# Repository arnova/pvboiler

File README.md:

# Open-source ESP PV-Boiler Controller

> ⚠️ **WARNING: HAZARDOUS VOLTAGES**
>
> This project is provided "as-is" and is to be used entirely at your own risk! The hardware is connected to the mains and involves voltages that may be lethal. Only build, install and service it if you are qualified to work on mains equipment, and always disconnect it from the mains before opening the enclosure.
>
> - The ESP/low-voltage side of the controller is galvanically isolated from the mains. Nevertheless, treat everything as live and dangerous!
> - Mount the controller in a closed plastic enclosure and earth the heatsink properly to the mains ground.
> - Only connect the controller to a correctly fused circuit.
> - The boiler's own thermostat and thermal cutoff must remain in the heating circuit. This controller is not a substitute for over-temperature protection!

This project is a complete hardware, firmware & software solution to turn your "dumb" electronic domestic hot water boiler into a smart **PV-Boiler**. It aims to optimize the amount of surplus solar electricity that can be stored in a boiler as hot water using as little grid power as possible.

Most other solutions use SSR modules for power control. This design uses a (BTA25/BTA40) **triac** for power control to enable **phase-angle control**, which allows for more accurate power control than with a normal SSR.

The hardware was designed using **KiCAD**, and the software uses **MQTT** for communication, targeted to be used with **Home Assistant**. The hardware and firmware were developed for either a NodeMCU v2 (Amica) ESP8266 module or an ESP32-DevKit (e.g. Olimex) module, but should in principle work with any ESP8266 or ESP32 board. Obviously, ESP boards with alternative form factors and/or pinouts cannot be directly fitted on the PCB but should be connected using wires, and you may need to modify platformio.ini and the GPIO definitions in include/system.h for your specific ESP board.

## Features

- Home Assistant (MQTT) support
- Phase angle control (default) or SSR dim style
- Configuration via USB serial connection or network terminal connection (port 8000)
- OTA updates (via PlatformIO)
- Support for an optional one-wire DS18B20 temperature sensor (probe) for sensing the boiler's internal temperature
- Automatic legionella prevention (using the optional one-wire temperature sensor). Danger zone temperatures, disinfection interval, duration and temperature are configurable via the terminal (see `exhelp`)
- Operating modes: automatic power budget mode (using e.g. P1/HA information), (manual) power percentage mode, boost mode (100% power, ignores software thermostat), standby mode (output off, legionella protection remains active) and off mode (output off, including legionella protection). The mode can be dynamically changed using MQTT
- Setpoint (software thermostat) modes (require the optional one-wire temperature sensor):
  - "Setpoint": always heats (100%) until the software thermostat setpoint is reached
  - "Budget up to Setpoint" / "Percentage up to Setpoint": like budget/percentage mode, but heating stops at the software thermostat setpoint
  - "Setpoint, then Budget": always heats (100%) until the software thermostat setpoint is reached; above it, surplus budget is used to heat further (up to the boiler's own thermostat)
  - "Percentage to Setpoint, then Budget": heats at the set percentage until the software thermostat setpoint is reached; above it, surplus budget is used to heat further (up to the boiler's own thermostat)
- Boiler overheating-protection (using the optional one-wire temperature sensor) in case the boiler hardware thermostat/protection somehow fails
- Support for directly communicating with DSMR-Reader (using MQTT) without e.g. Home Assistant
- Support for an optional OLED 128×64 screen to display output power/percentage, temperature and connection status
- The controller has a network watchdog. If there hasn't been any MQTT traffic to the controller for a while (e.g. when the network fails), the output will automatically decrease to 0% instead of being stuck on the last value. This behaviour can be disabled/configured with the `netwdt` and `netwdr` commands.

## Planned features & improvements

- Support for a CT current clamp
- Standalone support for more P1 providers

## Known issues

- During development it turned out that due to the ESP8266's single-core architecture WiFi interferes with accurate interrupt timing, causing problems with zero-cross detection and triac gate firing. Mitigations are in place but they can't completely fix the issue. Therefore for new designs it's recommended to use an ESP board with a dual-core ESP32-S3, ESP32-WROOM or ESP32-Wrover like the Olimex ESP32-DevKit-Lipo. Note that single-core ESP32 variants (e.g. ESP32-C3, ESP32-S2) share the ESP8266's limitation.

## Electromagnetic compatibility

Phase-angle control inherently generates harmonics and electromagnetic interference, because the triac switches the load on part-way through each mains half-cycle. The design includes an RC snubber across the triac and a 2-stage mains filter to limit this. Although such mains filters are expensive, do not omit them: consider the filter mandatory. Depending on your country and installation, regulations on conducted emissions and flicker (e.g. the EN 61000-3 series in the EU) may still apply to the complete installation, so check them before putting the device into permanent use.

## Hardware Assembly Hints

1. In the pictures-folder of this project you can find photos of my assembled enclosure which can be used as a guideline to build your own device
2. Use a sufficiently sized heatsink with a little thermal compound for mounting the BTA-triac. Generally it is recommended to use a heatsink with a thermal resistance better than 1.0 °C/W when using a ~2500 W boiler. Don't forget to connect the heatsink to the mains ground for safety! You should also use triacs with an electrically insulated tab, like the BTA-type triacs in the design
3. Around some power traces the mask has been intentionally left out. You should solder these traces with extra solder to reduce the power losses due to trace resistance
4. It is recommended to use 1.5 mm² flexible wires for internal wiring
5. When using the optional one-wire DS18B20 temperature sensor (probe) there are a few things you must adhere to make it work properly. Its supply should be connected to the board's +5V (not +3.3V), and the cable's ground shield should be connected to the (digital) low-voltage ground (NOT the mains ground) of the board. Most (sealed) temperature probes use a metal probe housing which is connected to the cable shield. Since this may short to the mains ground and introduce (switching) noise into the system, it should be isolated. The easiest way to accomplish this is using some shrink-tube
6. The electronics are designed for ~230/240 VAC grids. For other (lower) grid voltages some resistors (R1, R2, R11) need to be modified
7. The controller can only be connected directly to the normal mains connections of "dumb" hot water boilers. Boilers featuring any kind of (digital) electronics (except for an analog thermostat) require a modification of the boiler's internal wiring, see [Boilers with built-in electronics](#boilers-with-built-in-electronics)

## Boilers with built-in electronics

For boilers with (digital) electronics the controller cannot be connected to the boiler's normal mains connections. Instead, the controller must be placed in series with the boiler's heating element. This requires modifying the boiler's internal wiring:

1. Disconnect the boiler from the mains and make sure it cannot be switched on accidentally.
2. Of the 2 wires of the (internal) heating element(s), identify the one that is connected to the (safety) thermostat. This wire, and therefore the thermostat, must remain untouched.
3. Cut the other wire (the one NOT connected to the thermostat) in two. Connect only the end that goes to the heating element to the controller's TRIAC-L terminal.
4. Power the controller in one of these ways:
   - **Recommended: from the cut wire.** Connect the other cut end (the one coming from the boiler) to the controller's MAINS-L terminal, and connect the controller's MAINS-N terminal to the boiler's N (the connection the thermostat-side element wire returns to). The controller then only needs this one additional N connection. Because the controller takes its L from the same wire that used to feed the element, the L/N polarity pitfall of the separate feed option is avoided, which makes this option much more fool-proof. The cut end goes directly to the boiler's L input and is therefore permanently live; verify this with a multimeter before connecting.
   - **Separate feed.** Connect the controller's MAINS-L and MAINS-N terminals to the boiler's mains L and N, and properly insulate the unused cut end. Make sure the boiler's mains L/N connections are such that the controller's MAINS-L is the same "L" that used to feed the cut wire. Otherwise you create a short between the mains N and L.

Things to be aware of:

- The separate feed option is only suitable for a fixed (hard-wired) installation with verified polarity. Do **not** use it with a reversible plug (e.g. Schuko) where L and N are undefined. Always verify L and N with a multimeter.
- The boiler's own electronics may react unexpectedly to the modification (e.g. by reporting a fault when the element is not powered). This is boiler-dependent.
- Modifying a boiler's internal wiring may void its warranty and, depending on your country, may need to be performed by a qualified electrician.

Only do this when you have sufficient confidence you understand what you are doing!

## First Time Use

1. Flash the ESP firmware using PlatformIO. The initial flash needs to be performed using the USB serial connection, with one of the `usb-xxxxx` (`usb-esp8266` or `usb-esp32`) PlatformIO-environments: `pio run -e usb-xxxxx -t upload`. You may need to customize `platform` and `board` in your `platformio.ini` for your specific ESP board first.
2. After the initial flash, future firmware updates can be done over-the-air (OTA) with one of the `ota-xxxxx` (`ota-esp8266` or `ota-esp32`) PlatformIO-environments: `pio run -e ota-xxxxx -t upload`. Note that you *may* need to substitute the controller's IP address for `pvboiler.local` in `upload_port` of the relevant `ota-xxxxx` environment in case mDNS is not available in your network (or it's failing somehow).
3. Connect to the microcontroller's terminal interface, either via the USB connection or a socket connection to the device's IP at port 8000, using a terminal program (e.g. PuTTY). The network terminal is plain-text and also gives access to the stored WiFi and MQTT credentials, so only use it on a network you trust.
4. In the command terminal, `help` (+ `Enter`) will show all available commands with their descriptions. Initially, these operations must be performed:
   - Reset all settings to default with the `factoryreset`-command.
   - Set your WiFi network SSID with the `ssid`-command, providing the name of your network as an argument.
   - Set your WiFi network password with the `pass`-command, providing your network's security password as an argument. You may provide a zero-length value when your network requires no password.
   - Set your MQTT server IP with the `serverip`-command, providing the server IP as an argument.
   - Set your MQTT server username with the `mqttuser`-command. You may provide a zero-length value when your server requires no username.
   - Set your MQTT server password with the `mqttpass`-command. You may provide a zero-length value when your server requires no password.
   - Set boiler power rating with the `boiler`-command, providing the power rating of your boiler as an argument (the factory default is 2500 W).

> **Notes**
>
> - Only change other settings when you understand what they do!
> - When using budget logic mode, you must regularly (at least at 5-second intervals is recommended) tell the PvBoiler controller how much "budget" (= excess solar PV electricity) is available, e.g. from Home Assistant. A sample automation for Home Assistant can be found in the `home assistant` folder. Alternatively, use the terminal command `budgetsrc dsmr` to let the controller calculate the budget itself from DSMR-reader's MQTT topics (`dsmr/reading/electricity_currently_delivered` and `dsmr/reading/electricity_currently_returned`).

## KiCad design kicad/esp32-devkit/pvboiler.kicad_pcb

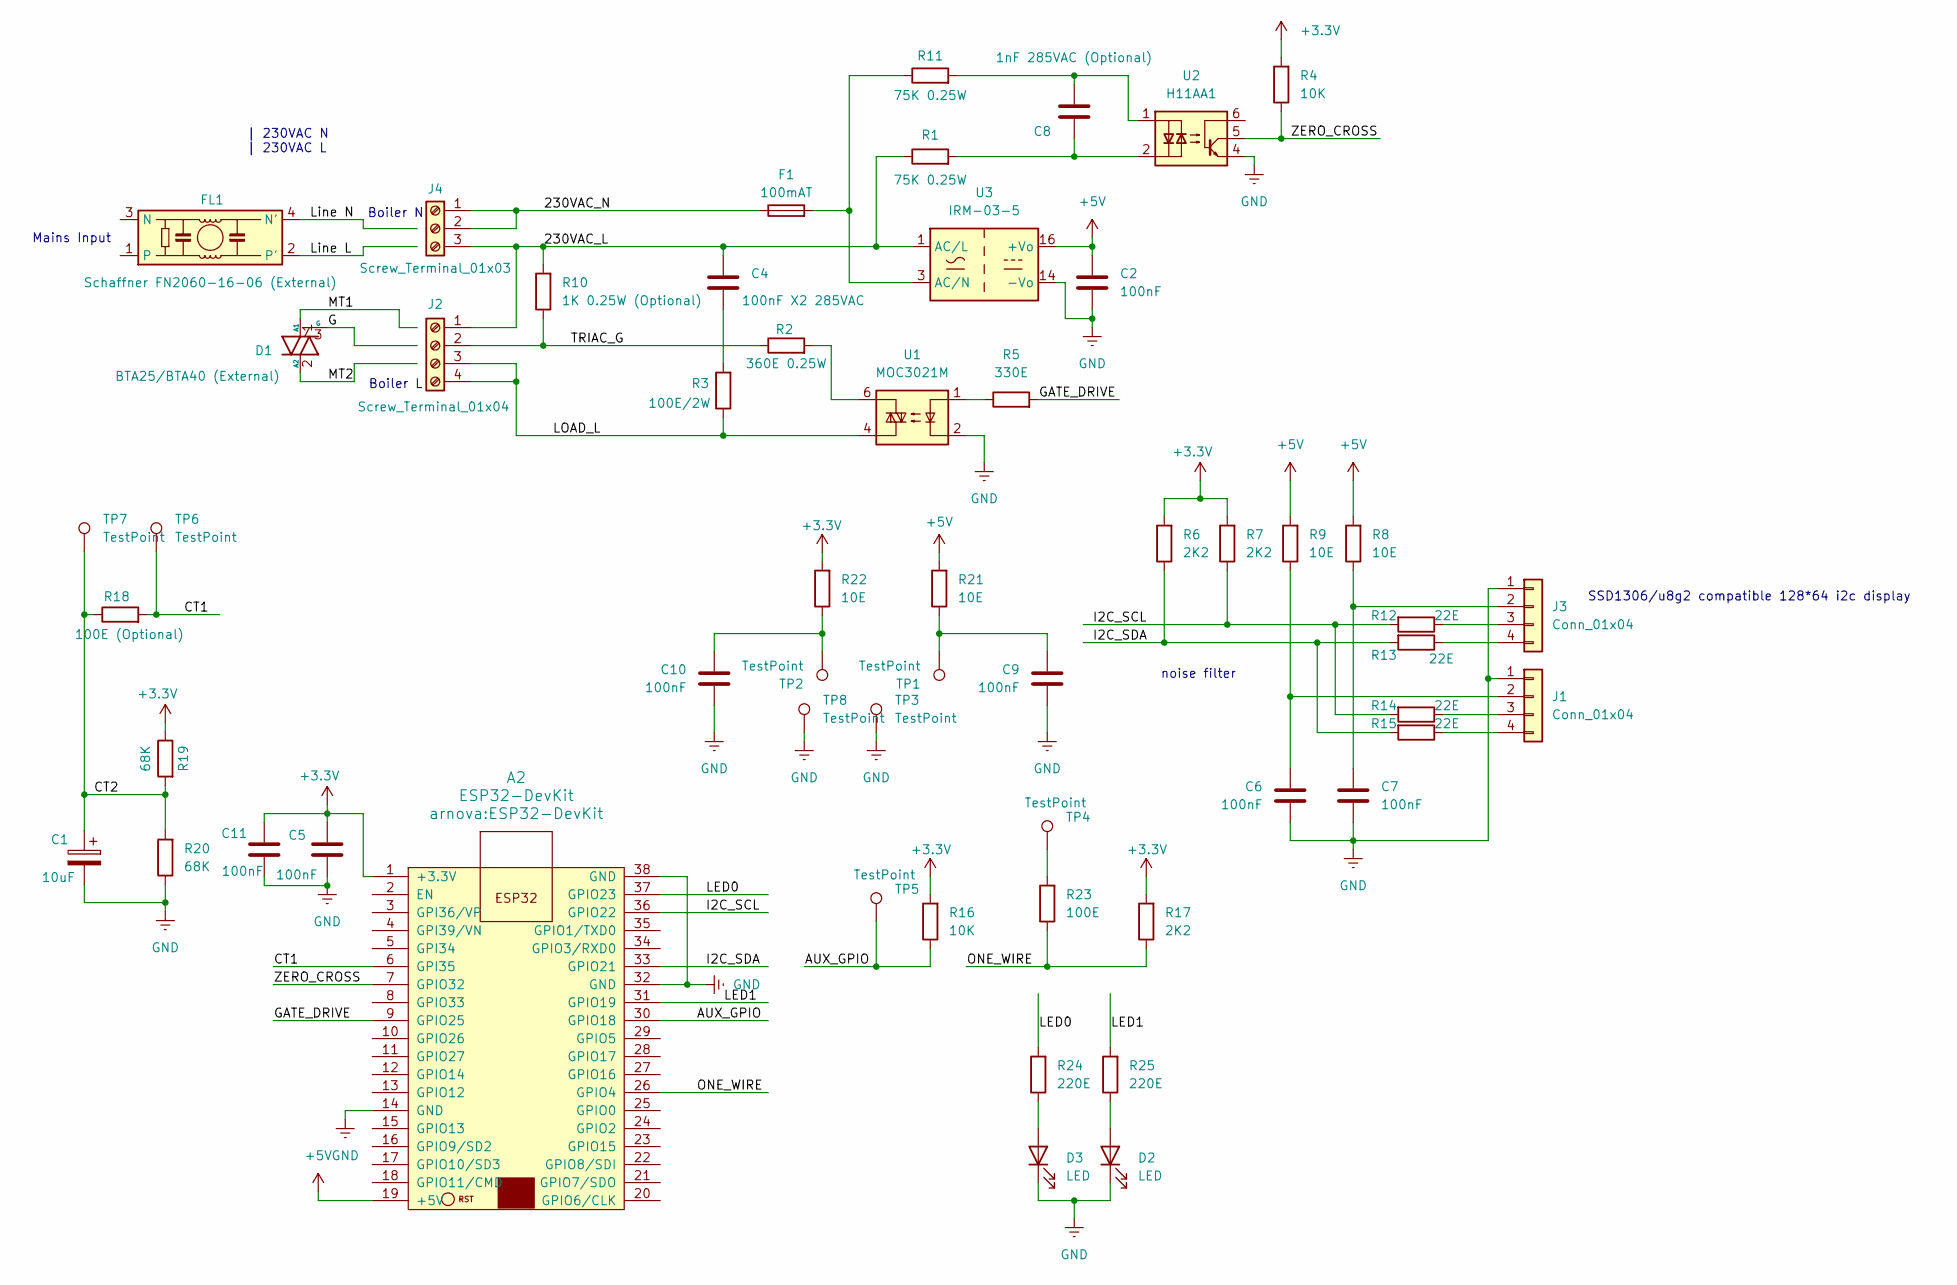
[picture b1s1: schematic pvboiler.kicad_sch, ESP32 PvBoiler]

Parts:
A2: ESP32-DevKit
C1: 10uF; CP_EIA-3216-18_Kemet-A_HandSolder
C2, C5, C6, C7, C9, C10, C11: 100nF; C_1206_3216Metric_Pad1.33x1.80mm_HandSolder
C4: 100nF X2 285VAC; C_Rect_L18.0mm_W8.0mm_P15.00mm_FKS3_FKP3
C8: 1nF 285VAC (Optional); C_Rect_L10.0mm_W4.0mm_P7.50mm_MKS4
D1: BTA25/BTA40 (External); PLCC-44_16.6x16.6mm_P1.27mm
D2, D3: LED; LED_1206_3216Metric
F1: 100mAT; Fuseholder_Cylinder-5x20mm_Schurter_0031_8201_Horizontal_Op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
FL1: Schaffner FN2060-16-06 (External); Filter_FILTERCON_1FPxx
J1, J3: Conn_01x04; Molex_KK-254_AE-6410-04A_1x04_P2.54mm_Vertical
J2: Screw_Terminal_01x04; TerminalBlock_Phoenix_MKDS-1,5-4-5.08_1x04_P5.08mm_Horizont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
J4: Screw_Terminal_01x03; TerminalBlock_Phoenix_MKDS-1,5-3-5.08_1x03_P5.08mm_Horizont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
R1, R11: 75K 0.25W; R_Axial_DIN0207_L6.3mm_D2.5mm_P10.16mm_Horizontal
R2: 360E 0.25W; R_Axial_DIN0207_L6.3mm_D2.5mm_P10.16mm_Horizontal
R3: 100E/2W; R_Axial_DIN0414_L11.9mm_D4.5mm_P15.24mm_Horizontal
R4, R16: 10K; R_1206_3216Metric
R5: 330E; R_1206_3216Metric
R6, R7, R17: 2K2; R_1206_3216Metric
R8, R9, R21, R22: 10E; R_1206_3216Metric
R10: 1K 0.25W (Optional); R_Axial_DIN0207_L6.3mm_D2.5mm_P10.16mm_Horizontal
R12, R13, R14, R15: 22E; R_1206_3216Metric
R18: 100E (Optional); R_1206_3216Metric
R19, R20: 68K; R_1206_3216Metric
R23: 100E; R_1206_3216Metric
R24, R25: 220E; R_1206_3216Metric
TP1, TP2, TP3, TP4, TP5, TP6, TP7, TP8: TestPoint; TestPoint_THTPad_D2.5mm_Drill1.2mm
U1: MOC3021M; DIP-6_W7.62mm
U2: H11AA1; DIP-6_W7.62mm
U3: IRM-03-5; Converter_ACDC_MeanWell_IRM-03-xx_THT

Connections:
+3.3V: A2.1 (+3.3V), C5.1, C11.1, R4.2, R6.2, R7.2, R16.2, R17.2, R19.1, R22.2
+5V: A2.19 (+5V), C2.1, R8.2, R9.2, R21.2, U3.16 (+Vo)
/230VAC_L: C4.2, J2.1, J4.3, R1.1, R10.2, U3.1 (AC/L)
/230VAC_N: F1.1, J4.1, J4.2
/AUX_GPIO: A2.30 (GPIO18), R16.1, TP5.1 (1_1)
/CT1: A2.6 (GPI35), R18.2, TP6.1 (1_1)
/CT2: C1.1, R18.1, R19.2, R20.2, TP7.1 (1_1)
/GATE_DRIVE: A2.9 (GPIO25), R5.2
/I2C_SCL: A2.36 (GPIO22), R7.1, R12.2, R14.2
/I2C_SDA: A2.33 (GPIO21), R6.1, R13.2, R15.2
/LED0: A2.37 (GPIO23), R24.2
/LED1: A2.31 (GPIO19), R25.2
/LOAD_L: J2.3, J2.4, R3.1, U1.4
/ONE_WIRE: A2.26 (GPIO4), R17.1, R23.1
/TRIAC_G: J2.2, R2.1, R10.1
/ZERO_CROSS: A2.7 (GPIO32), R4.1, U2.5
GND: A2.14 (GND), A2.32 (GND), A2.38 (GND), C1.2, C2.2, C5.2, C6.2, C7.2, C9.2, C10.2, C11.2, D2.1 (K), D3.1 (K), J1.1, J3.1, R20.1, TP3.1 (1_1), TP8.1 (1_1), U1.2, U2.4, U3.14 (-Vo)
unnamed: C4.1, R3.2
unnamed: C8.1, R11.2, U2.1
unnamed: C8.2, R1.2, U2.2
unnamed: C9.1, R21.1, TP1.1 (1_1)
unnamed: C10.1, R22.1, TP2.1 (1_1)
unnamed: D2.2 (A), R25.1
unnamed: D3.2 (A), R24.1
unnamed: C6.1, J1.2, R9.1
unnamed: J1.3, R14.1
unnamed: J1.4, R15.1
unnamed: C7.1, J3.2, R8.1
unnamed: J3.3, R12.1
unnamed: J3.4, R13.1
unnamed: R2.2, U1.6
unnamed: R5.1, U1.1
unnamed: R23.2, TP4.1 (1_1)
unnamed: F1.2, R11.1, U3.3 (AC/N)

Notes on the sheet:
SSD1306/u8g2 compatible 128*64 i2c display
| 230VAC N | 230VAC L
Boiler N
noise filter
Boiler L
Mains Input

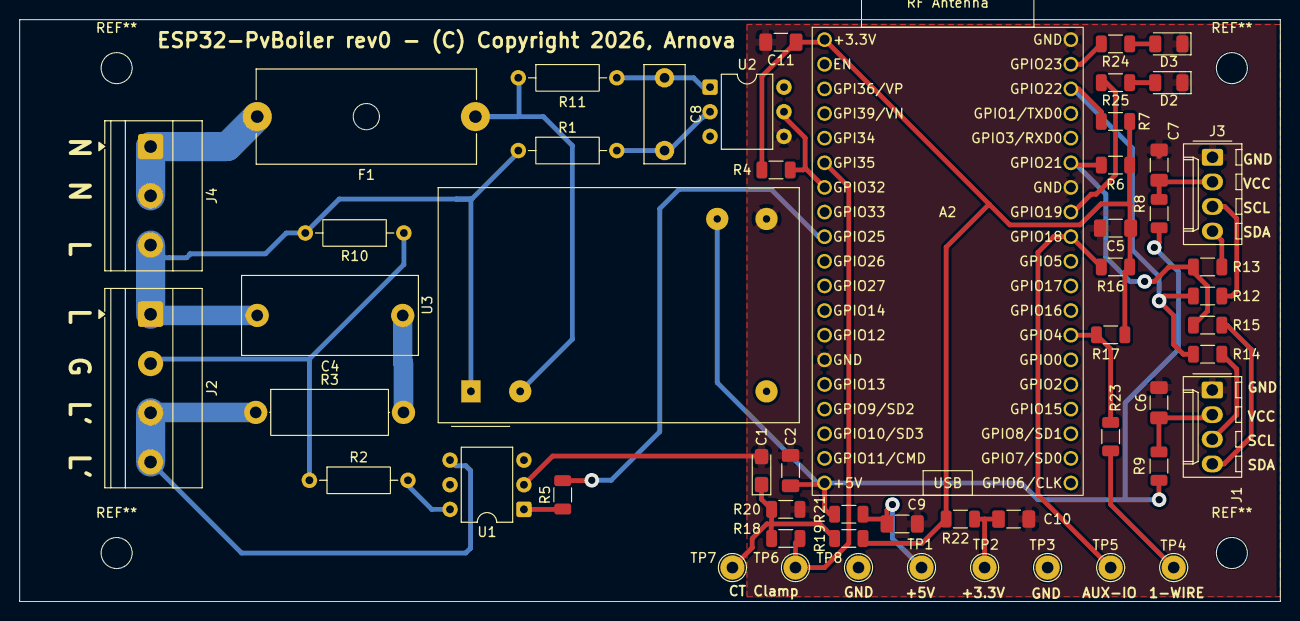
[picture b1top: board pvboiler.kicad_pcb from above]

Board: 2 copper layers, 130.0 x 60.0 mm, 54 parts (0 on the bottom side), 34 nets.

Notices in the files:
kicad/esp32-devkit/pvboiler.kicad_pcb:
ESP32-PvBoiler rev0 - (C) Copyright 2026, Arnova
